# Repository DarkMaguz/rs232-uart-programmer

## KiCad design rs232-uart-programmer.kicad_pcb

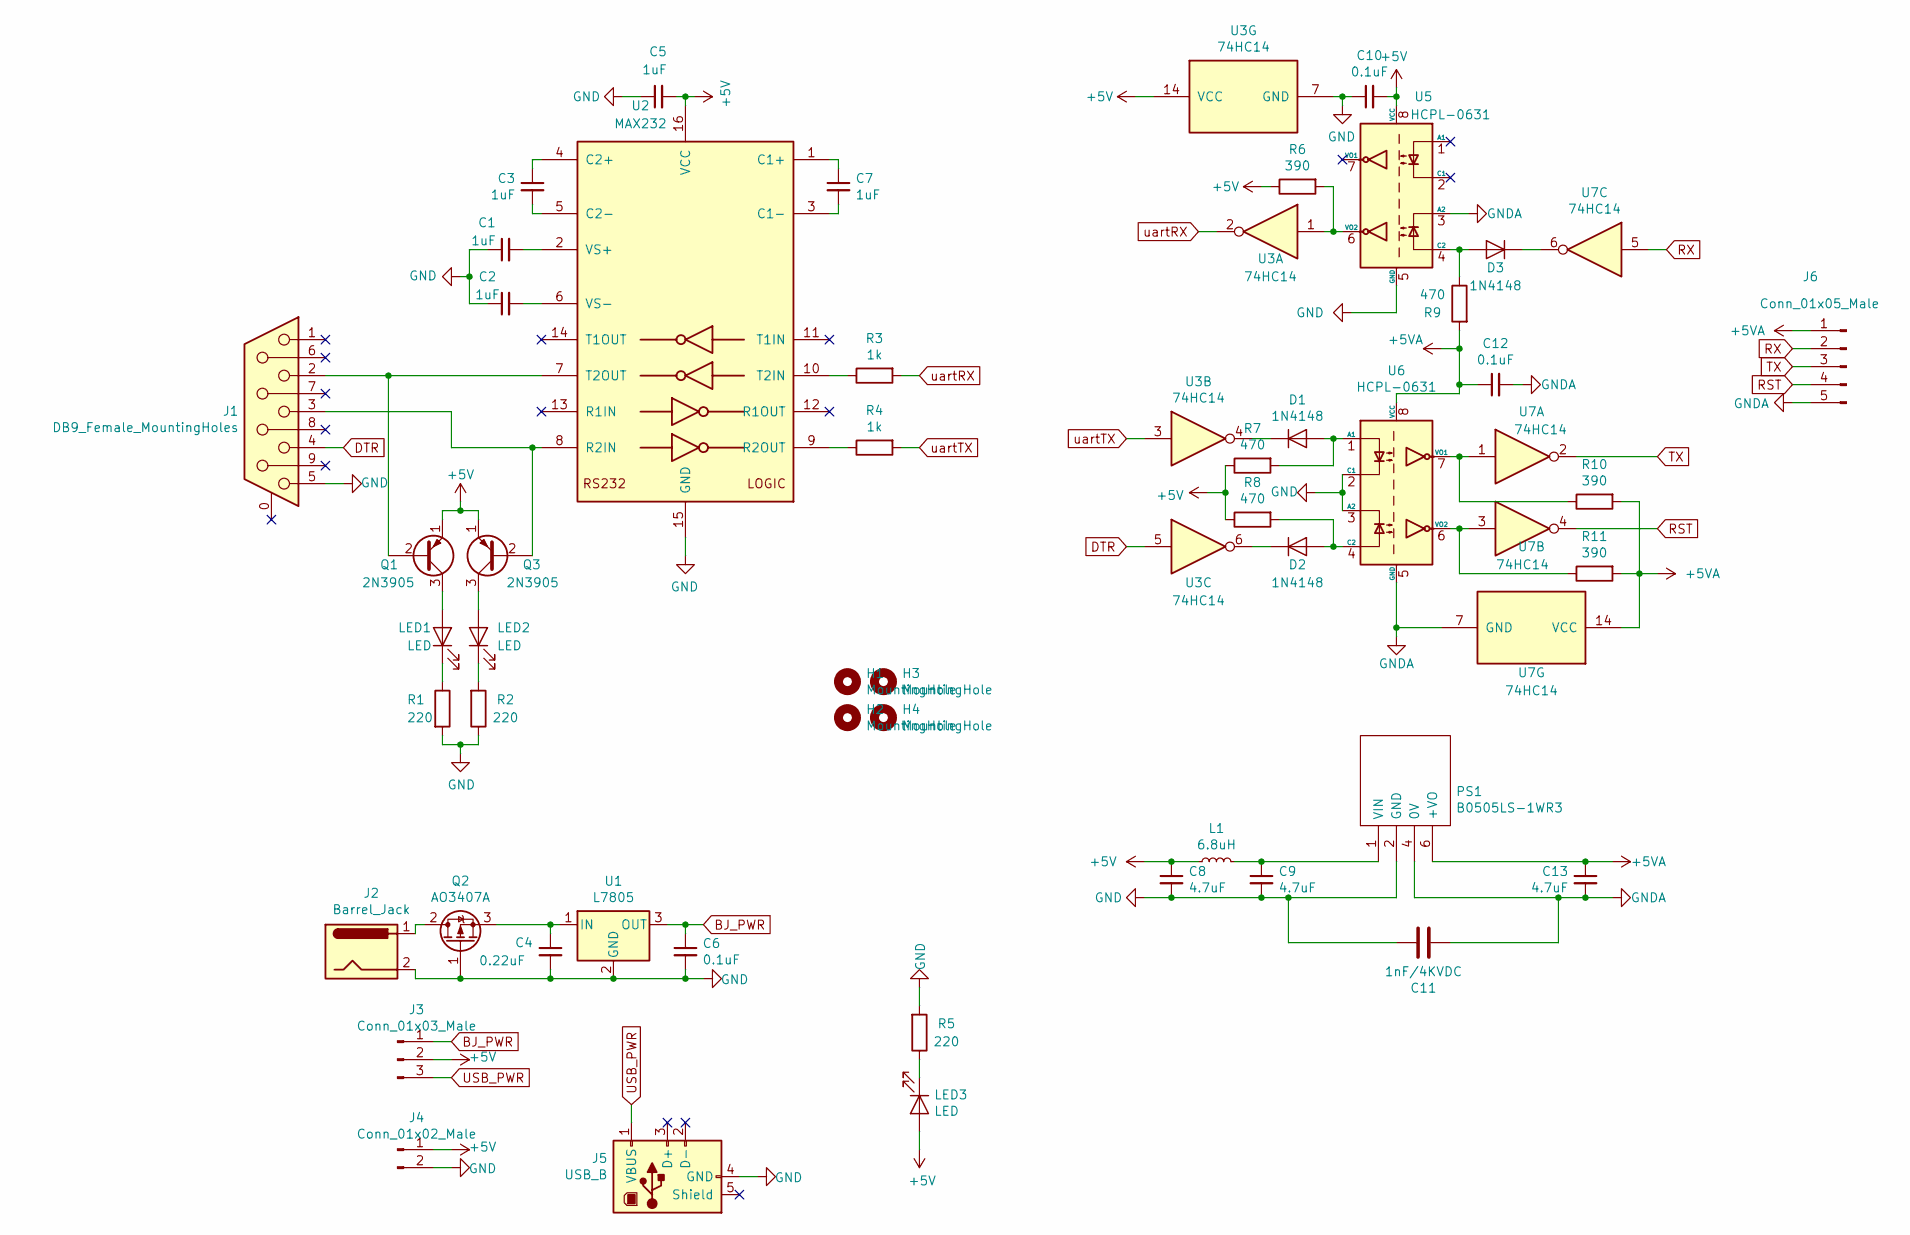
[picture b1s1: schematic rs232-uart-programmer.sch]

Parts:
C1, C2, C3, C5, C7: 1uF; C_Disc_D5.1mm_W3.2mm_P5.00mm
C4: 0.22uF; C_Disc_D5.1mm_W3.2mm_P5.00mm
C6, C10, C12: 0.1uF; C_Disc_D5.1mm_W3.2mm_P5.00mm
C8, C9, C13: 4.7uF; C_Disc_D5.1mm_W3.2mm_P5.00mm
C11: 1nF/4KVDC; C_Disc_D14.5mm_W5.0mm_P10.00mm
D1, D2, D3: 1N4148; D_DO-35_SOD27_P7.62mm_Horizontal
H1, H2, H3, H4: MountingHole; MountingHole_3mm
J1: DB9_Female_MountingHoles; DSUB-9_Female_Horizontal_P2.77x2.84mm_EdgePinOffset9.90mm_H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
J2: Barrel_Jack; BarrelJack_Horizontal
J3: Conn_01x03_Male; PinHeader_1x03_P2.54mm_Vertical
J4: Conn_01x02_Male; PinHeader_1x02_P2.54mm_Vertical
J5: USB_B; USB_B_OST_USB-B1HSxx_Horizontal
J6: Conn_01x05_Male; PinHeader_1x05_P2.54mm_Vertical
L1: 6.8uH; L_Toroid_Vertical_L16.4mm_W7.6mm_P6.60mm_Vishay_TJ3
LED1, LED2, LED3: LED; LED_D5.0mm
PS1: B0505LS-1WR3; B0505LS1WR3; Manufacturer_Part_Number B0505LS-1WR3
Q1, Q3: 2N3905; TO-92_Inline
Q2: AO3407A; SOT-23
R1, R2, R5: 220; R_Axial_DIN0207_L6.3mm_D2.5mm_P10.16mm_Horizontal
R3, R4: 1k; R_Axial_DIN0207_L6.3mm_D2.5mm_P10.16mm_Horizontal
R6, R10, R11: 390; R_Axial_DIN0207_L6.3mm_D2.5mm_P10.16mm_Horizontal
R7, R8, R9: 470; R_Axial_DIN0207_L6.3mm_D2.5mm_P10.16mm_Horizontal
U1: L7805; TO-220-3_Vertical
U2: MAX232; DIP-16_W7.62mm
U3, U7: 74HC14; DIP-14_W7.62mm
U5, U6: HCPL-0631; SOIC-8_3.9x4.9mm_P1.27mm

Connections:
+5V: C5.2, C8.1, C10.2, J3.2, J4.1, L1.1, LED3.2 (A), Q1.1 (E), Q3.1 (E), R6.1, R7.1, R8.1, U2.16 (VCC), U3.14 (VCC), U5.8 (VCC)
+5VA: C12.1, C13.1, J6.1, PS1.6 (+VO), R9.2, R10.2, R11.2, U6.8 (VCC), U7.14 (VCC)
BJ_PWR: C6.1, J3.1, U1.3 (OUT)
DTR: J1.4, U3.5
GND: C1.1, C2.1, C4.2, C5.1, C6.2, C8.2, C9.2, C10.1, C11.1, J1.5, J2.2, J4.2, J5.4 (GND), PS1.2 (GND), Q2.1 (G), R1.2, R2.1, R5.2, U1.2 (GND), U2.15 (GND), U3.7 (GND), U5.5 (GND), U6.2 (C1), U6.3 (A2)
GNDA: C11.2, C12.2, C13.2, J6.5, PS1.4 (0V), U5.3 (A2), U6.5 (GND), U7.7 (GND)
unnamed: C1.2, U2.2 (VS+)
unnamed: C2.2, U2.6 (VS-)
unnamed: C3.1, U2.4 (C2+)
unnamed: C3.2, U2.5 (C2-)
unnamed: C4.1, Q2.3 (S), U1.1 (IN)
unnamed: C7.1, U2.1 (C1+)
unnamed: C7.2, U2.3 (C1-)
unnamed: C9.1, L1.2, PS1.1 (VIN)
unnamed: D1.1 (K), U3.4
unnamed: D1.2 (A), R7.2, U6.1 (A1)
unnamed: D2.1 (K), U3.6
unnamed: D2.2 (A), R8.2, U6.4 (C2)
unnamed: D3.1 (K), U7.6
unnamed: D3.2 (A), R9.1, U5.4 (C2)
unnamed: J1.2, Q1.2 (B), U2.7 (T2OUT)
unnamed: J1.3, Q3.2 (B), U2.8 (R2IN)
unnamed: J2.1, Q2.2 (D)
unnamed: LED1.1 (K), R1.1
unnamed: LED1.2 (A), Q1.3 (C)
unnamed: LED2.1 (K), R2.2
unnamed: LED2.2 (A), Q3.3 (C)
unnamed: LED3.1 (K), R5.1
unnamed: R3.1, U2.10 (T2IN)
unnamed: R4.1, U2.9 (R2OUT)
unnamed: R6.2, U3.1, U5.6 (VO2)
unnamed: R10.1, U6.7 (VO1), U7.1
unnamed: R11.1, U6.6 (VO2), U7.3
RST: J6.4, U7.4
RX: J6.2, U7.5
TX: J6.3, U7.2
USB_PWR: J3.3, J5.1 (VBUS)
uartRX: R3.2, U3.2
uartTX: R4.2, U3.3

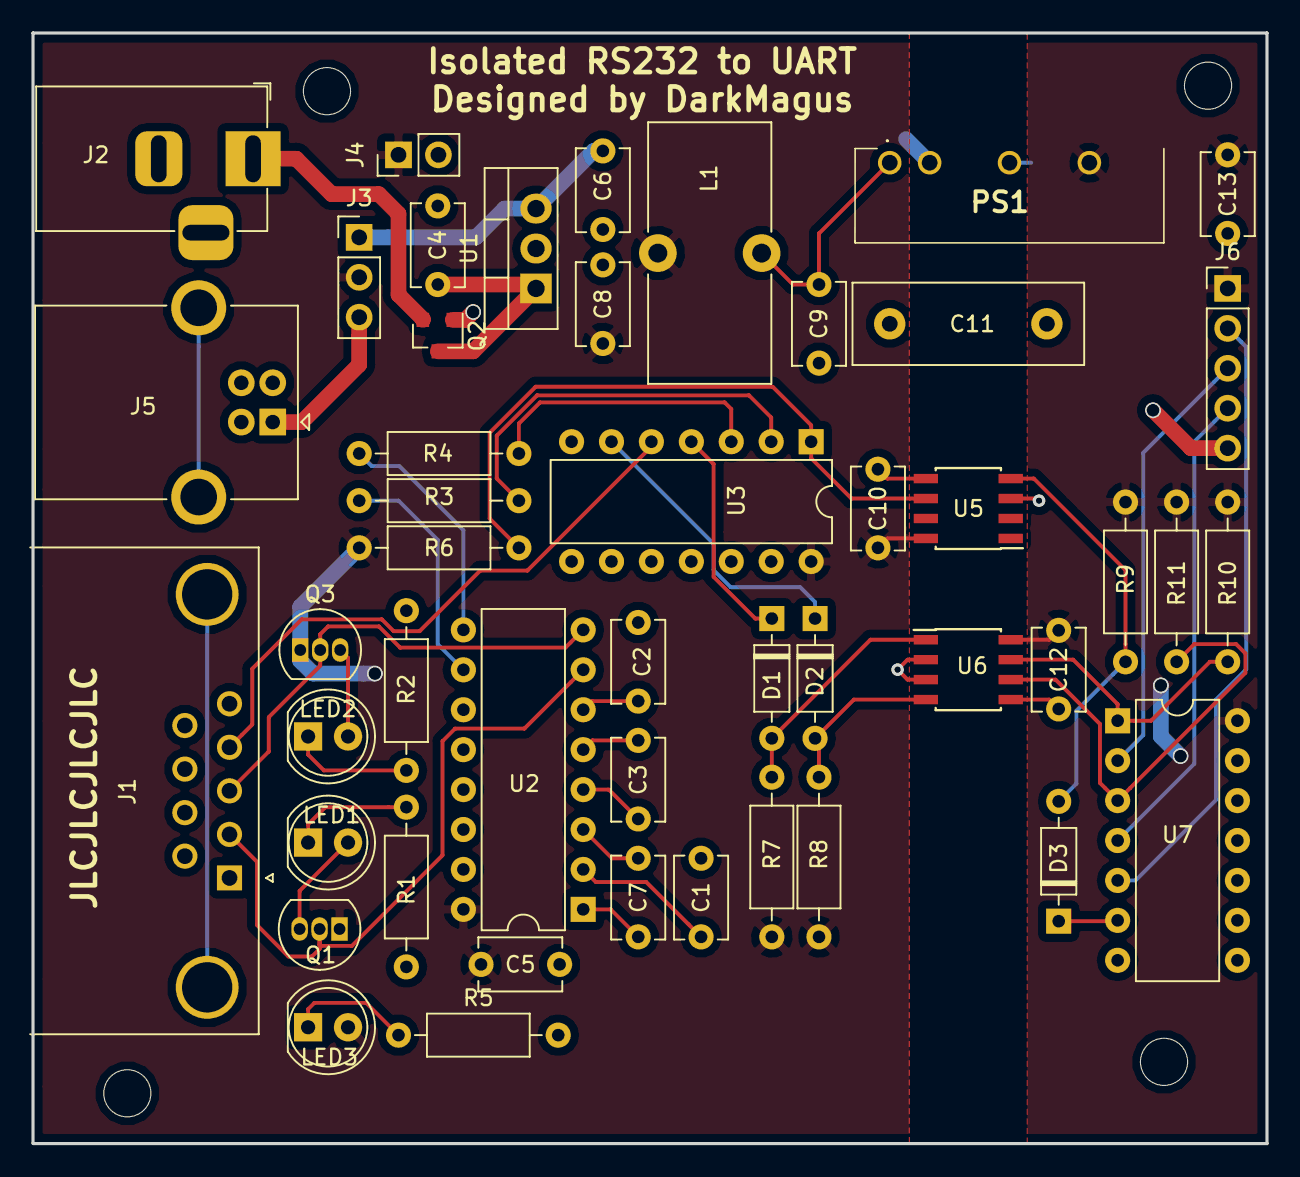
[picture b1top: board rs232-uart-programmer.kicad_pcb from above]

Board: 2 copper layers, 78.5 x 70.7 mm, 51 parts (0 on the bottom side), 39 nets.

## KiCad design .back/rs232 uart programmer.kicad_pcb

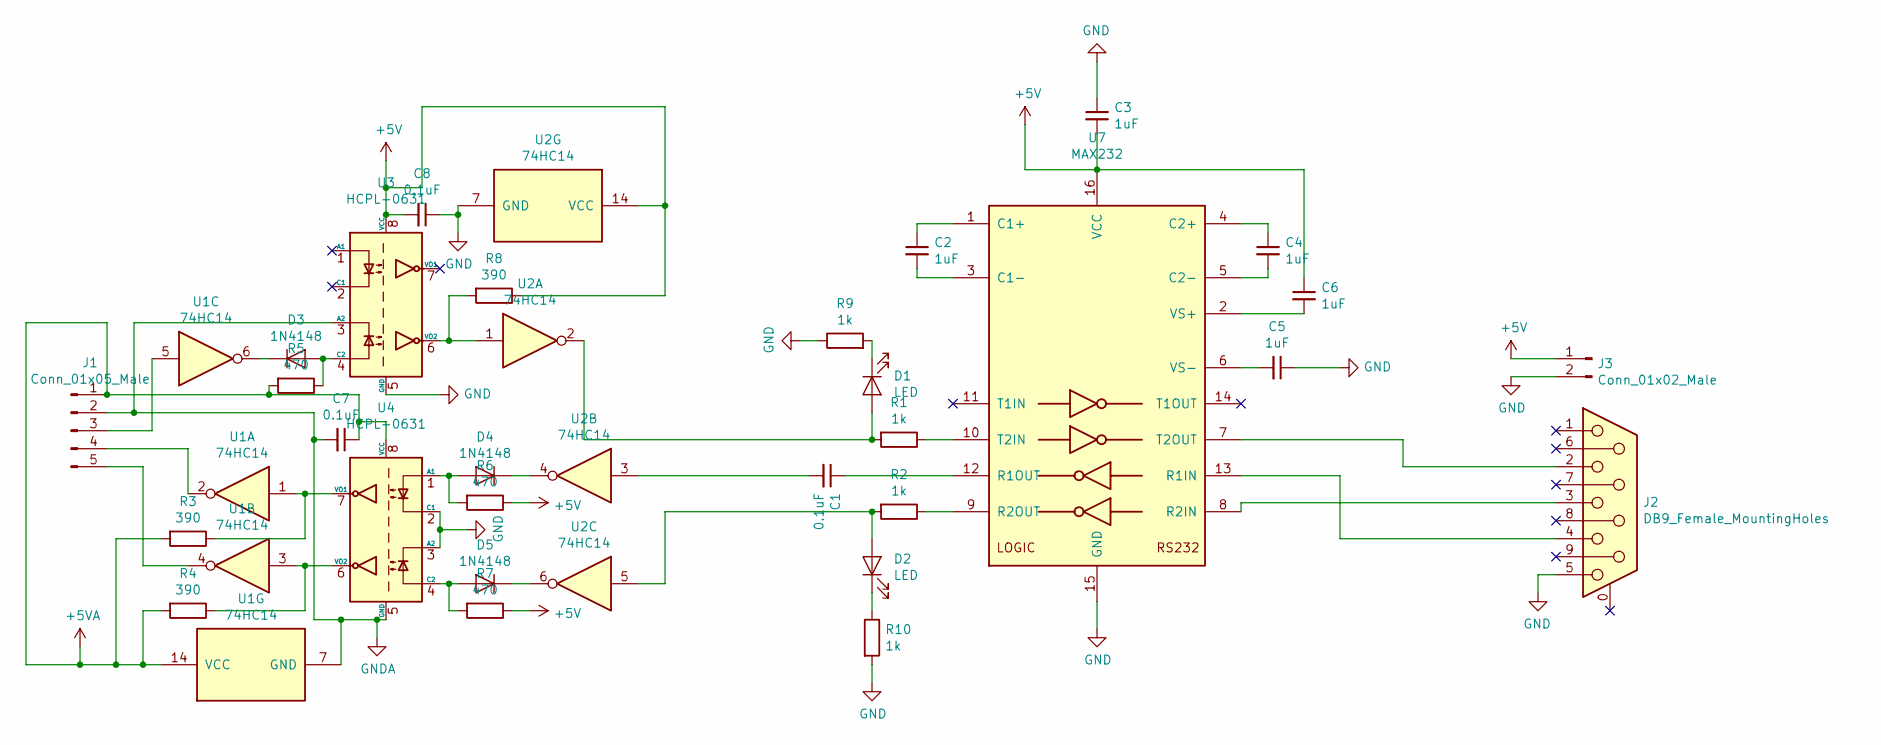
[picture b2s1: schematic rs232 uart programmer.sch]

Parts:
C1, C7, C8: 0.1uF; C_Disc_D5.1mm_W3.2mm_P5.00mm
C2, C3, C4, C5, C6: 1uF; C_Disc_D5.1mm_W3.2mm_P5.00mm
D1, D2: LED; LED_D5.0mm
D3, D4, D5: 1N4148; D_DO-35_SOD27_P7.62mm_Horizontal
J1: Conn_01x05_Male; PinHeader_1x05_P2.54mm_Vertical
J2: DB9_Female_MountingHoles; DSUB-9_Female_Horizontal_P2.77x2.84mm_EdgePinOffset9.90mm_H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
J3: Conn_01x02_Male; PinHeader_1x02_P2.54mm_Vertical
R1, R2, R9, R10: 1k; R_Axial_DIN0414_L11.9mm_D4.5mm_P15.24mm_Horizontal
R3, R4, R8: 390; R_Axial_DIN0414_L11.9mm_D4.5mm_P15.24mm_Horizontal
R5, R6, R7: 470; R_Axial_DIN0414_L11.9mm_D4.5mm_P15.24mm_Horizontal
U1, U2: 74HC14; DIP-14_W7.62mm_Socket
U3, U4: HCPL-0631; SOIC-8_3.9x4.9mm_P1.27mm
U7: MAX232; DIP-16_W7.62mm_Socket

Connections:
+5V: C3.2, C6.1, C8.2, J3.1, R6.1, R7.1, R8.1, U2.14 (VCC), U3.8 (VCC), U7.16 (VCC)
+5VA: C7.1, J1.1, R3.2, R4.2, R5.2, U1.14 (VCC), U4.8 (VCC)
GND: C3.1, C5.1, C8.1, J2.5, J3.2, R9.1, R10.2, U2.7 (GND), U3.5 (GND), U4.2 (C1), U4.3 (A2), U7.15 (GND)
GNDA: C7.2, J1.2, U1.7 (GND), U3.3 (A2), U4.5 (GND)
unnamed: C1.1, U7.12 (R1OUT)
unnamed: C1.2, U2.3
unnamed: C2.1, U7.1 (C1+)
unnamed: C2.2, U7.3 (C1-)
unnamed: C4.1, U7.4 (C2+)
unnamed: C4.2, U7.5 (C2-)
unnamed: C5.2, U7.6 (VS-)
unnamed: C6.2, U7.2 (VS+)
unnamed 12: D1.1 (K), R9.2; also elsewhere on the board
unnamed 13: D1.2 (A), R1.2, U2.2; also elsewhere on the board
unnamed 14: D2.1 (K), R10.1; also elsewhere on the board
unnamed 15: D2.2 (A), R2.2, U2.5; also elsewhere on the board
unnamed: D3.1 (K), U1.6
unnamed: D3.2 (A), R5.1, U3.4 (C2)
unnamed: D4.1 (K), U2.4
unnamed: D4.2 (A), R6.2, U4.1 (A1)
unnamed: D5.1 (K), U2.6
unnamed: D5.2 (A), R7.2, U4.4 (C2)
unnamed: J1.3, U1.5
unnamed: J1.4, U1.2
unnamed: J1.5, U1.4
unnamed: J2.2, U7.7 (T2OUT)
unnamed: J2.3, U7.8 (R2IN)
unnamed: J2.4, U7.13 (R1IN)
unnamed: R1.1, U7.10 (T2IN)
unnamed: R2.1, U7.9 (R2OUT)
unnamed: R3.1, U1.1, U4.7 (VO1)
unnamed: R4.1, U1.3, U4.6 (VO2)
unnamed: R8.2, U2.1, U3.6 (VO2)

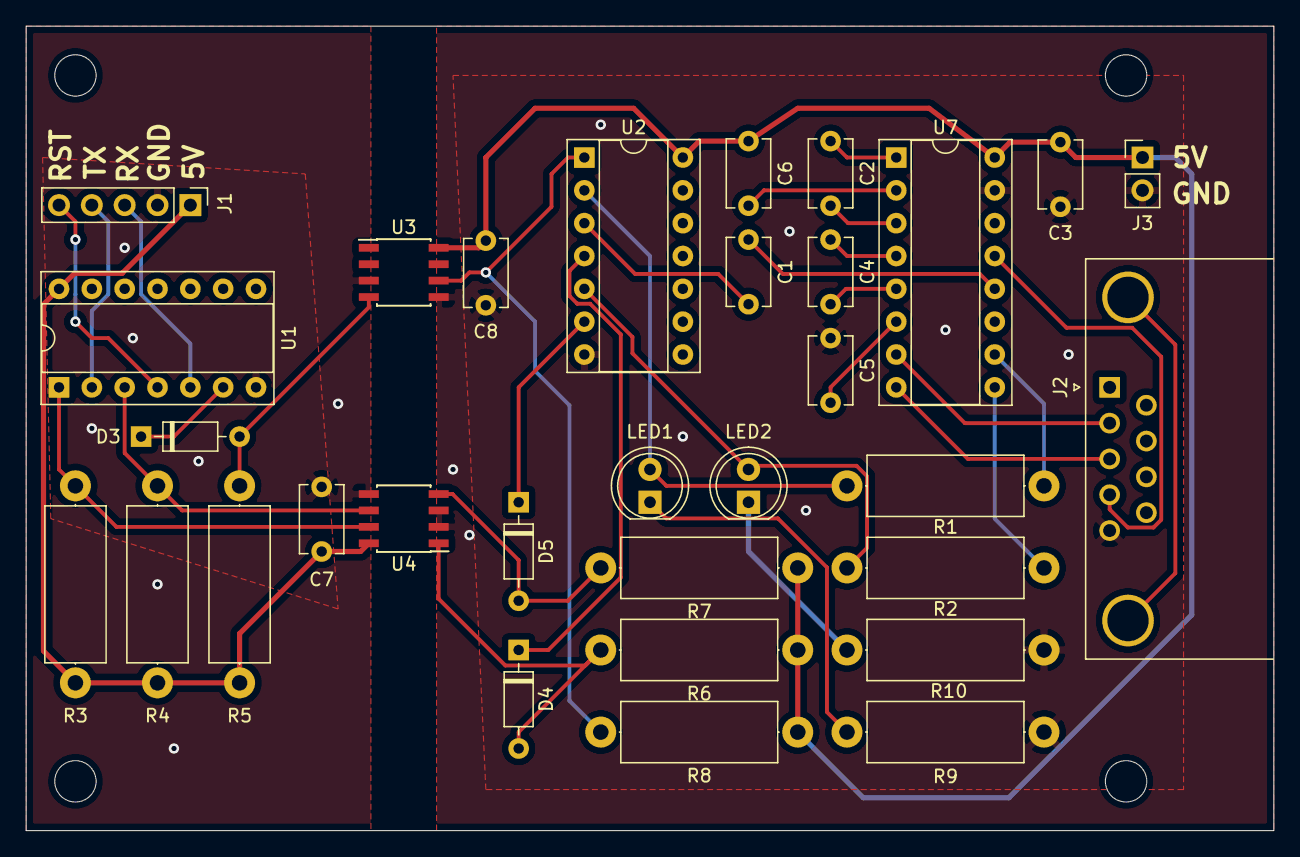
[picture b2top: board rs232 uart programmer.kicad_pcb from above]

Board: 2 copper layers, 96.5 x 62.2 mm, 31 parts (0 on the bottom side), 33 nets.

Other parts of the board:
LED1, LED2: LED; LED_D5.0mm

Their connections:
unnamed 12: LED1.1; also elsewhere on the board
unnamed 13: LED1.2; also elsewhere on the board
unnamed 14: LED2.1; also elsewhere on the board
unnamed 15: LED2.2; also elsewhere on the board

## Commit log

2021-09-12 Rev 2
2021-09-12 Added Silkscreen description
2021-09-12 Added mounting holes
